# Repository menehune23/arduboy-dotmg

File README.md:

**dotMG** is an

```// Arduboy-compatible```

```// cartridge-based```

```// hackable```

DIY game console!

> More pictures in the [assets](assets) folder!

Designed to remind you of the early days of handheld gaming, dotMG combines game cartridges with Arduboy greatness!

## Features

- Swappable game cartridges based on the Arduino Pro Micro (including reverse cart protection)

- Hackability via EXT header (exposes SPI/I2C/GPIO pins) -- add your own crank, accelerometer, joystick, flash chip, RGB LED, or any other add-on of your own creation!

- Rechargeable battery (with play 'n charge capability via load-sharing circuitry)

- Analog volume control

- Large 2.44" 128x64 high-contrast OLED display

## Documentation

Select one of the following to learn how to build and use dotMG

- [Build Guide](docs/build.md)
- [Usage Guide](docs/usage.md)
- [PCB Ordering Guide](docs/pcb-ordering.md)
- [Custom Shell Guide](docs/custom-shell.md)

## Reporting Issues

If you've found a hardware/software bug, have feedback, or if you just need help troubleshooting, please [file an issue](https://github.com/menehune23/arduboy-dotmg/issues). I'm just one person, so I'll try to respond as best as I can (bugs will take priority over feedback and troubleshooting).

## License

Copyright (c) 2021 Andrew Meyer.

[Attribution-NonCommercial-ShareAlike 4.0 International (CC BY-NC-SA 4.0)](https://creativecommons.org/licenses/by-nc-sa/4.0/)

This project is for DIYers and hobbyists. It may not be used for anything considered commercial use without the author's explicit, written consent. Otherwise, use at your own risk and have fun!

**This project is not officially licensed or endorsed by [Arduboy](https://arduboy.com).**

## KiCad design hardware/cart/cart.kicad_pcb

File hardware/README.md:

# Hardware

This directory contains the hardware design files for dotMG. To use the files here to order PCBs, see the [PCB Ordering Guide](/docs/pcb-ordering.md).

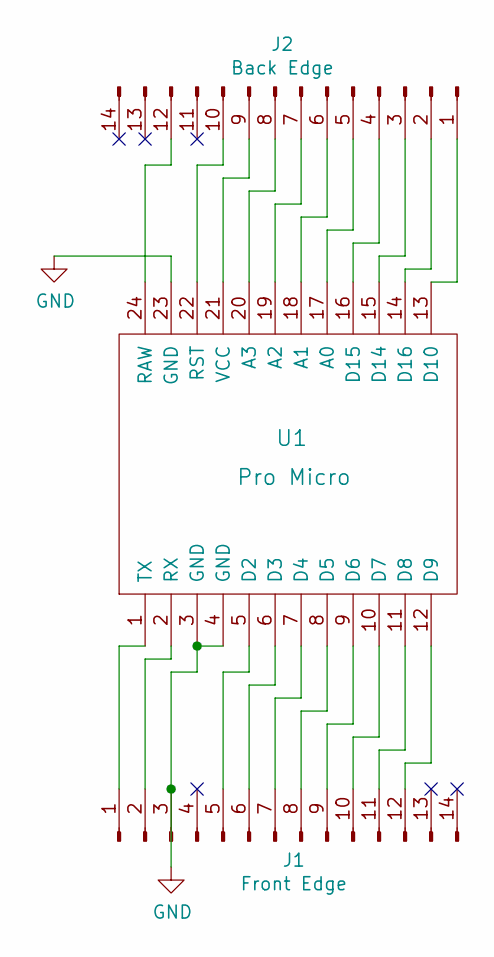
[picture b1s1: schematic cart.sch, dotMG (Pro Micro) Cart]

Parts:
J1: Front Edge; CARD_CONNECTOR_14_POS
J2: Back Edge; CARD_CONNECTOR_14_POS
U1: Pro Micro; PRO_MICRO

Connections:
GND: J1.3, U1.3 (GND), U1.4 (GND), U1.23 (GND)
unnamed: J1.1, U1.1 (TX)
unnamed: J1.2, U1.2 (RX)
unnamed: J1.5, U1.5 (D2)
unnamed: J1.6, U1.6 (D3)
unnamed: J1.7, U1.7 (D4)
unnamed: J1.8, U1.8 (D5)
unnamed: J1.9, U1.9 (D6)
unnamed: J1.10, U1.10 (D7)
unnamed: J1.11, U1.11 (D8)
unnamed: J1.12, U1.12 (D9)
unnamed: J2.1, U1.13 (D10)
unnamed: J2.2, U1.14 (D16)
unnamed: J2.3, U1.15 (D14)
unnamed: J2.4, U1.16 (D15)
unnamed: J2.5, U1.17 (A0)
unnamed: J2.6, U1.18 (A1)
unnamed: J2.7, U1.19 (A2)
unnamed: J2.8, U1.20 (A3)
unnamed: J2.9, U1.21 (VCC)
unnamed: J2.10, U1.22 (RST)
unnamed: J2.12, U1.24 (RAW)

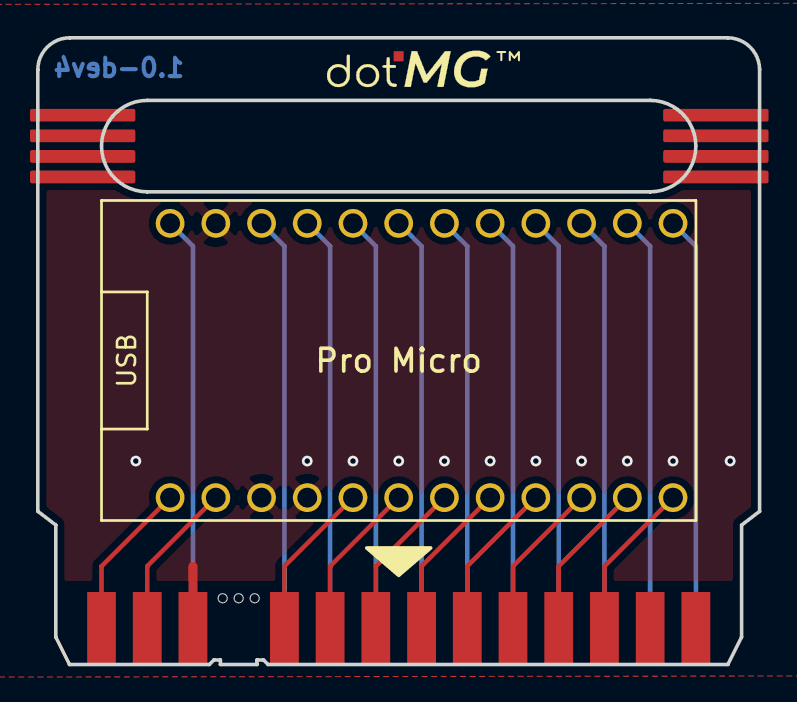
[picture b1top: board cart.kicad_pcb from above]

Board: 2 copper layers, 40.1 x 34.8 mm, 3 parts (1 on the bottom side), 22 nets.

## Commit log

2021-01-19 Cart schematic
2021-01-19 Add initial cart layout
2021-01-19 Update readme, license
2021-01-19 Correct gerber name
2021-01-19 Update license
2021-01-21 Add breakaway key pin filler
2021-01-31 Initial system schematic
2021-02-05 Initial board layout (needs routing)
2021-02-09 Route system board
2021-02-10 OLED RES -> RST (board), break out RX/D0
2021-02-11 System front/back, extend cart height
2021-02-11 Update main board button labels
2021-02-11 Add JLC order number lables
2021-02-11 Fix a via position
2021-02-12 Bump system to 1.0-dev1
    - Mirror charge symbol on back shell
    - Remove button 3D models
2021-02-12 Rewire screen regulator Vin to RAW
    - Also add schematic PDFs
2021-02-12 Remove accidental WIP changes
2021-02-12 Connect power to VCC instead of RAW
2021-02-12 Revert WIP readme changes (again)
2021-02-13 Connect display RES to D0/RX
2021-02-13 Add more license details
2021-02-13 Add board package source
2021-02-13 Fix display reset
2021-02-13 Add board index JSON and updater script
2021-02-13 Fix package index
2021-02-13 Fix package base URL
2021-02-13 Clean out unused variants
2021-02-14 Update system PCB, fix speaker cutout
2021-02-14 Update EXT footprint
2021-02-18 Add usage and build info to readme
2021-03-05 Add grip slot to cart
    - Extends cart by 0.24 in
    - Update to 1.0-dev1
2021-03-05 Update system board (start of 1.0dev4)
    - Cover cart connector more
    - Move EXT labels closer to edge
    - Add cart grip cutout
2021-03-08 Finish 1.0-dev4 updates
    - Add stylistic display cutout
    - Add support under charger board
2021-03-08 Increase cart grip top thickness to ~3.5mm
2021-03-08 Update readme and BOM
2021-03-08 Update soldering notes
2021-03-08 Update cart breakaway tab to use drills (1.0-dev2)
2021-04-13 Update system and cart
    - Shorten cart by 1mm to account for other connector brand
    - Use 1-pin header for charger board support
    - Fix diode footprint
    - Bump cart/system versions (no gerbers yet)
2021-04-13 Update BOM
2021-04-13 Add gerbers and updated schematics
2021-06-08 Remove 3.3V regulator
2021-07-12 Rename to dotMG
2021-07-12 Fix erroneous compilation issues
2021-07-12 Finalize support for no RGB LED
2021-07-12 Set RGB LED pins to low inputs when not in use
2021-07-12 Move power/reset buttons inward slightly
2021-07-12 wip; layout adjustment
2021-07-12 wip; save
2021-07-12 Correct typo in readme
2021-07-14 wip; layout (needs routing)
2021-07-14 wip; fix ext footprints
2021-07-17 wip; routed
2021-07-17 wip; board height adjust
2021-07-18 wip; front/back covers
2021-07-18 wip; gerbers
2021-07-18 wip; ext pin cutout
2021-07-18 wip; update readme
2021-07-18 Add GBA style system
2021-07-27 Flip EXT pin labels (advance)
2021-11-12 Update BOM and README
2021-11-12 Reorganize documentation
2021-11-12 Update build guide
2021-11-12 Fix broken links
2021-11-12 Small typo
2021-11-12 Update usage guide
2021-11-12 Update images in readme
2021-11-14 Add shell design files
2021-11-14 Update docs
    - Add shell ordering guide
    - Update links
    - Update BOM
2021-11-14 Update shell docs
2021-11-15 Add pinouts and EXT info
2021-11-15 Update image alignment
2021-11-15 Update text alignment
2021-11-15 Fix image/text alignment
2021-11-15 Fix text alignment
2021-11-15 Update board package
    Changes "RGB LEDs" to "RGB LED"
2021-11-15 Update board package
    Changes "RGB LEDs" to "RGB LED" in menu
2021-11-15 Update package index
    Remove email
2021-11-15 Fix broken link
2021-11-15 Update shell files
2021-11-16 Add official Arduboy board
2021-11-16 Update default bootloader option
2021-11-16 Fix typo
2021-11-16 Fix official Arduboy support
2021-11-16 Update board list in package index
2021-11-16 Update usage guide: pin initialization
2021-11-16 Update formatting
2021-11-16 Fix support for SPI add-ons
    No longer hogs SPI bus for display. Instead, keeps the display CS raised, and asserts only when needed.
2021-11-19 Add version check to update-index.py
2021-11-19 Add support for BeepPin2 in Arduboy2 library
2021-11-21 Minor board updates
    - Add logo to main board
    - Increase breakaway tab width (better for fabs)
2021-11-21 Add EPS shell files
2021-11-21 Update shell guide
2021-12-04 Fix bootloader
2022-05-21 Add system-1.0-dev7-without-shell
    This PCB will print stsyem without shell, it gonna reduce some cost.
